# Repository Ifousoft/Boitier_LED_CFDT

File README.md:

# Boitier_LED_CFDT
Boitier autonome avec une LED clignotante au passage d'une personne devant un panneau d'affichage pour inciter à lire le panneau

L'objectif est la réalisation d'un petit boitier autonome fonctionnant sur piles à accrocher sur un panneau d'affichage CFDT.
Lorsqu'une personne passe devant le panneau, le capteur de présence réveille le système, la LED clignote pour indiquer qu'une nouvelle information a été affichée. Le système se rendors automatiquement pour économiser les piles.

Le système s'arrête automatiquement et se mets en sommeil après 2 jours d'utilisation, considérant que l'information n'est plus suffisamment récente.

Dans le cas d'un nouvel affichage, il suffit d'appuyer sur le bouton et le sytème rédémarre pour 2 jours.

D'après les calculs, le boitier devrait fonctionner sur pile pendant environ 1 an. Dans le cas où la pile CR2032 pour l'horloge est usée, au démarrage du système, le LED clignotera sans s'arrêter.

Le boitier comprends un arduino pour la partie processeur, une LED, orange (forcément), un bouton de réinitialisation et un mini capteur PIR pour détecter les passages des personnes.

PS: ayant réalisé une première version mais sans horloge, j'ai fais cette seconde version. Le code fonctionne et le schéma électronique est OK.
Néanmoins, je n'ai pas testé la réalisation du PCB ni vérifier l'impression 3D du boitier pour valider l'assemblage de tous les composants.
N'hesitez pas à effectuer des modifications si nécessaire.

Ifousoft.

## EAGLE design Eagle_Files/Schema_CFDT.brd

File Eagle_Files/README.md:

Fichiers Eagle pour la conception du schéma électronique et du PCB.

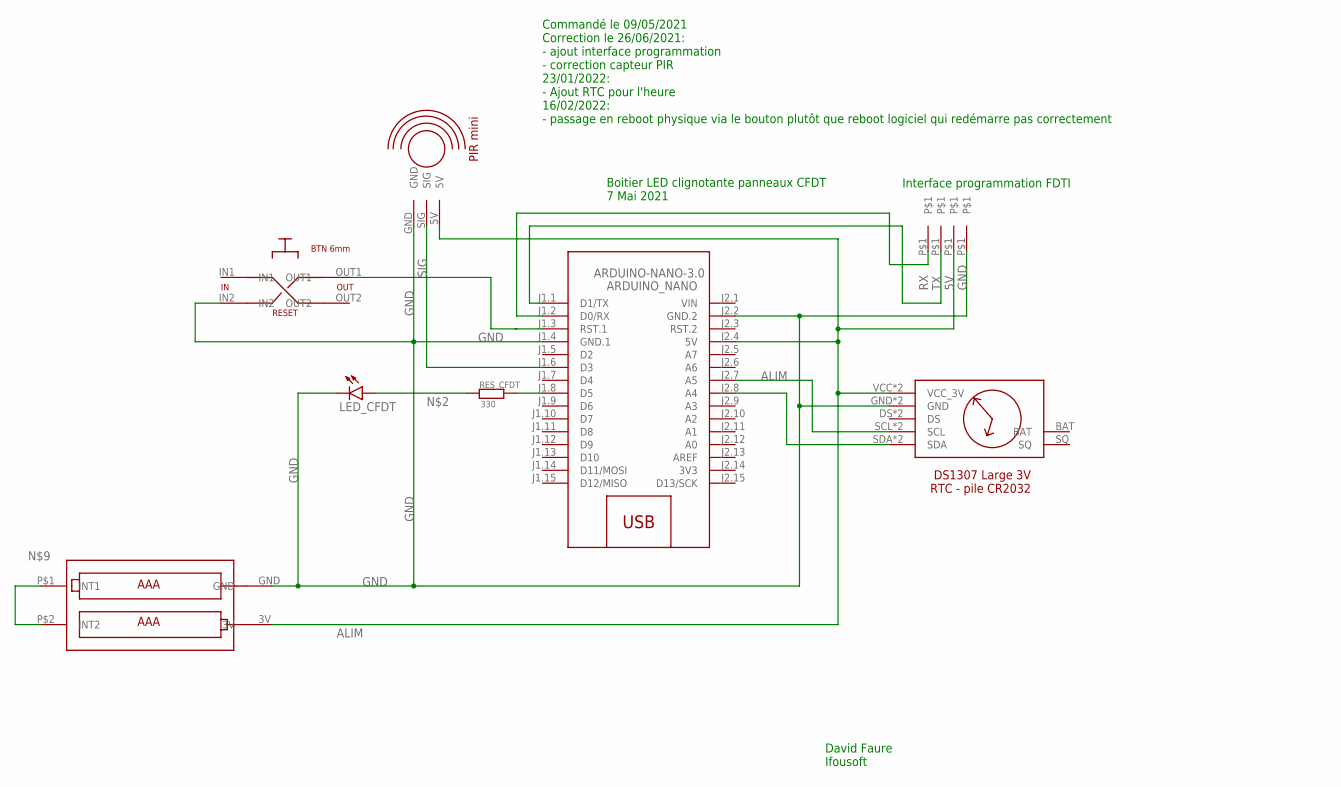
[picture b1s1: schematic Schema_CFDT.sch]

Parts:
5V: IFOU_PIN
ARDUINO_NANO: ARDUINO-NANO-3.0
GND: IFOU_PIN_GNDIFOU_PIN_GND2; IFOU_PIN_GND
LED_CFDT: IFOU_LED3MM; LED3MM
RESET: IFOU_SWITCH_6MM
RES_CFDT: 330; RESISTOR
RX: IFOU_PIN
TX: IFOU_PIN
U$2: IFOU_2XAAA_HOLDER
U$3: IFOU_MINI_PIR
U$4: IFOU_DS1307_RTC_3V

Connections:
3V3: ARDUINO_NANO.J2.14 (3V3)
ALIM: 5V.P$1, ARDUINO_NANO.J2.4 (5V), U$2.3V, U$3.5V, U$4.VCC (VCC_3V), U$4.VCC@2 (VCC_3V)
GND: ARDUINO_NANO.J1.4 (GND.1), ARDUINO_NANO.J2.2 (GND.2), GND.P$1, LED_CFDT.K (C), RESET.IN2, U$2.GND, U$3.GND, U$4.GND, U$4.GND@2 (GND)
unnamed: ARDUINO_NANO.J1.8 (D5), RES_CFDT.PIN2
unnamed: LED_CFDT.A, RES_CFDT.PIN1
unnamed: ARDUINO_NANO.J1.3 (RST.1), RESET.OUT1
unnamed: ARDUINO_NANO.J2.8 (A4), U$4.SDA, U$4.SDA@2 (SDA)
unnamed: ARDUINO_NANO.J2.7 (A5), U$4.SCL, U$4.SCL@2 (SCL)
unnamed: U$2.P$1 (INT1), U$2.P$2 (INT2)
RX: ARDUINO_NANO.J1.2 (D0/RX), RX.P$1
SIG: ARDUINO_NANO.J1.6 (D3), U$3.SIG
TX: ARDUINO_NANO.J1.1 (D1/TX), TX.P$1
VIN: ARDUINO_NANO.J2.1 (VIN)

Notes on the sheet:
Boitier LED clignotante panneaux CFDT 7 Mai 2021
Commandé le 09/05/2021 Correction le 26/06/2021: - ajout interface programmation - correction capteur PIR 23/01/2022: - Ajout RTC pour l'heure 16/02/2022: - passage en reboot physique via le bouton plutôt que reboot logiciel qui redémarre pas correctement
Interface programmation FDTI
David Faure Ifousoft

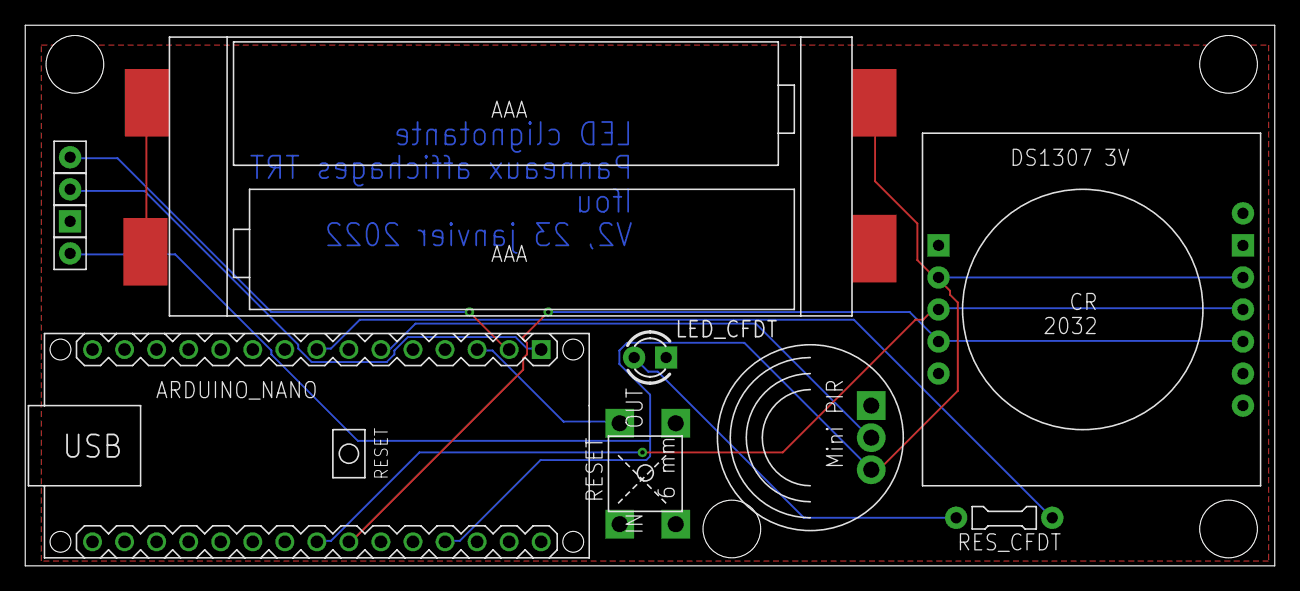
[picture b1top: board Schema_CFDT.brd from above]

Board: 2 copper layers, 99.0 x 42.9 mm, 11 parts (0 on the bottom side), 11 nets.

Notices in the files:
parts and their libraries:
diy-modules: Released under the Creative Commons Attribution 4.0 International License: http://creativecommons.org/licenses/by/4.0
